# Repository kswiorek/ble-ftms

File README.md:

# Arduino BLE Indoor Bike Fitness Machine

This project uses two ESP32 boards to emulate an expensive indoor bike trainer and a power meter.<br/>
<br/>
One ESP measures power and cadence on a crank, the other receives these values, emulates a trainer and forwards the data. It also receives the simulation parameter from a computer and sets position of the resistance screw accordingly.<br/>
The data is also displayed on a 12864 screen and the user is able to change the resistance in ERG mode and the gears in simulation mode.<br/>
The user can also load a file with resistance values and times when to set them on an SD card.<br/>
The whole "realistic physics" part turned out to be more annoying to set up than realistic, so I added a configurator, with which the user can graphicaly define the function converting from the simulated grade to the resistance. More described in the instructable.
<br/><br/>
The promissed instructable <a href="https://www.instructables.com/DIY-Indoor-Bike-Smart-Trainer/?cb=1604870523">https://www.instructables.com/DIY-Indoor-Bike-Smart-Trainer/?cb=1604870523</a>

If you want to dig deaper into the code I highly suggest reading the "Fitness Machine Service" specifications
<a href="https://www.bluetooth.com/specifications/gatt/">https://www.bluetooth.com/specifications/gatt/</a>

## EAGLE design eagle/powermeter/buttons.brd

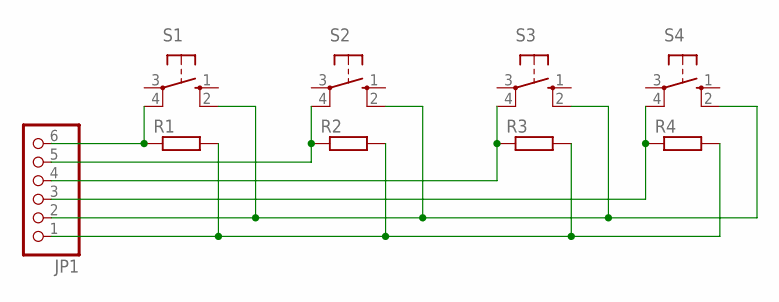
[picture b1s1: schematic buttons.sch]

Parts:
JP1: PINHD-1X6/90; 1X06/90
R1, R2, R3, R4: R-EU_0207/10; 0207/10
S1, S2, S3, S4: 10-XX; B3F-10XX

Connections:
unnamed: JP1.6, R1.1, S1.4 (P1)
unnamed: JP1.5, R2.1, S2.4 (P1)
unnamed: JP1.4, R3.1, S3.4 (P1)
unnamed: JP1.3, R4.1, S4.4 (P1)
unnamed: JP1.2, S1.2 (S1), S2.2 (S1), S3.2 (S1), S4.2 (S1)
unnamed: JP1.1, R1.2, R2.2, R3.2, R4.2

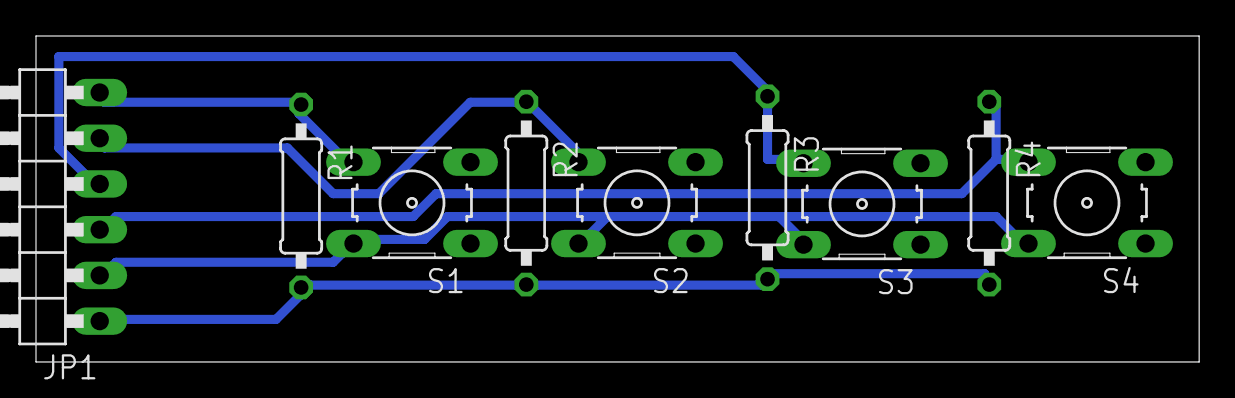
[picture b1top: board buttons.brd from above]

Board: 2 copper layers, 64.6 x 18.1 mm, 9 parts (0 on the bottom side), 6 nets.

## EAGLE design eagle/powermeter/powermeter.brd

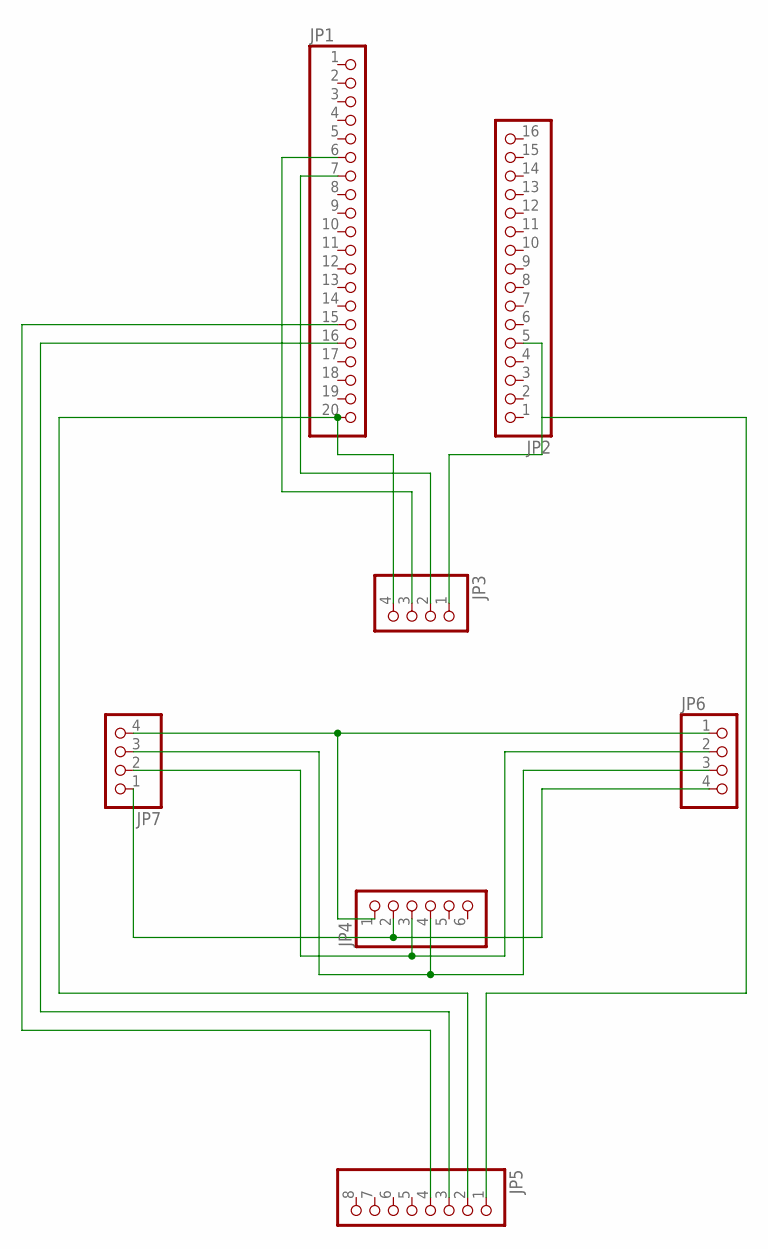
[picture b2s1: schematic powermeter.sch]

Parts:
JP1: PINHD-1X20; 1X20
JP2: PINHD-1X16; 1X16
JP3, JP6, JP7: PINHD-1X4; 1X04
JP4: PINHD-1X6; 1X06
JP5: PINHD-1X8; 1X08

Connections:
unnamed: JP4.1, JP6.1, JP7.4
unnamed: JP4.2, JP6.4, JP7.1
unnamed: JP4.3, JP6.2, JP7.2
unnamed: JP4.4, JP6.3, JP7.3
unnamed: JP1.20, JP3.4, JP5.2
unnamed: JP1.6, JP3.3
unnamed: JP1.7, JP3.2
unnamed: JP1.15, JP5.4
unnamed: JP2.5, JP3.1, JP5.1
unnamed: JP1.16, JP5.3

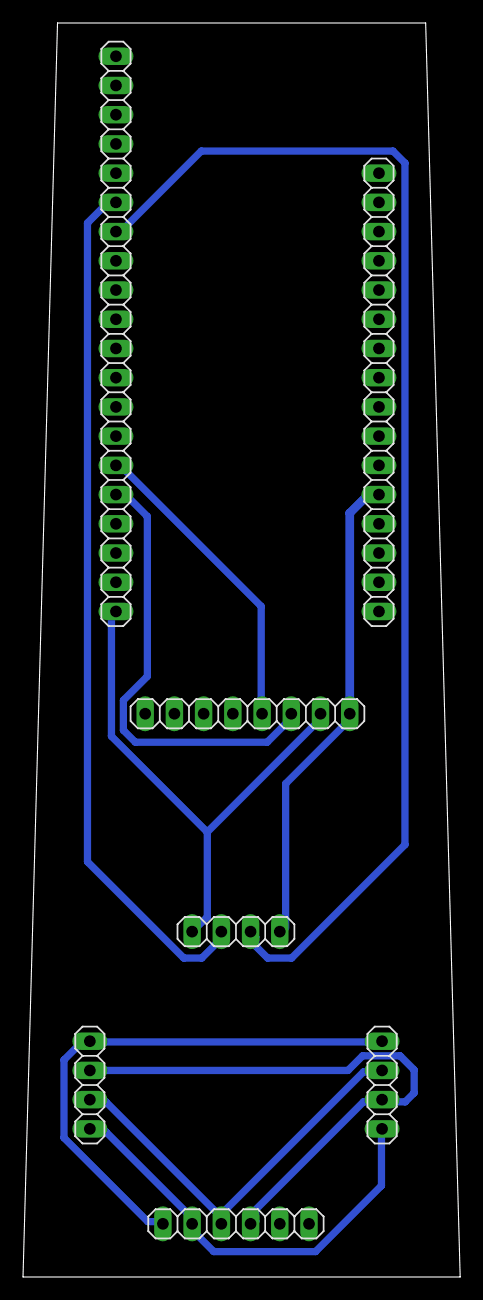
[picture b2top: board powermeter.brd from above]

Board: 2 copper layers, 38.0 x 109.0 mm, 7 parts (0 on the bottom side), 10 nets.

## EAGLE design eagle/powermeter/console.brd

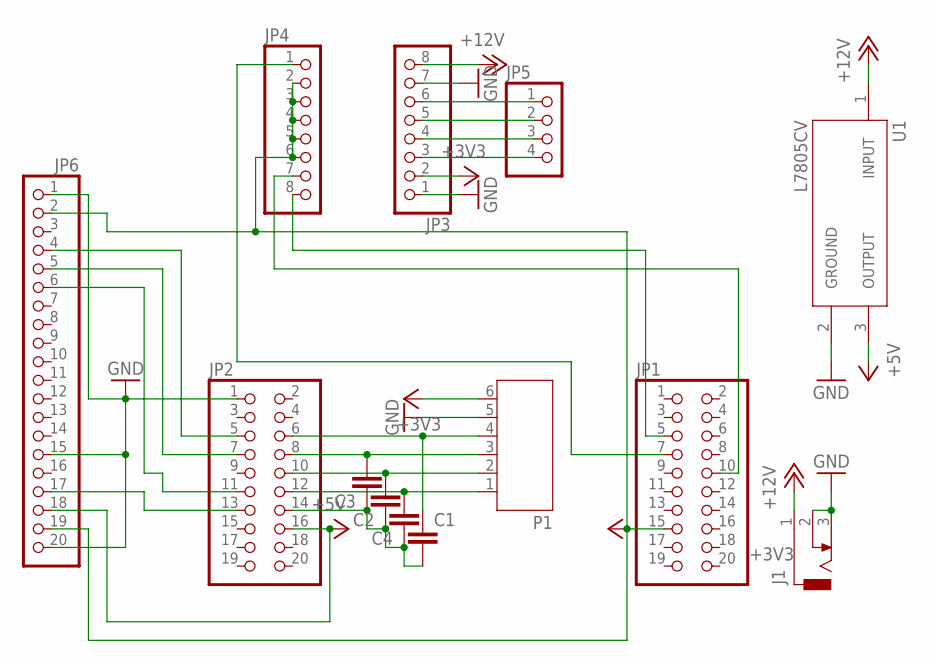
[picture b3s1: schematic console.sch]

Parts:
C1, C2, C3, C4: C-EU025-030X050; C025-030X050
J1: DCJ0303
JP1, JP2: PINHD-2X10; 2X10
JP3, JP4: PINHD-1X8; 1X08
JP5: PINHD-1X4/90; 1X04/90
JP6: PINHD-1X20; 1X20
P1: JST-PH6
U1: L7805CV; TO255P1040X460X1968-3

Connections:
+3V3: JP1.15, JP3.2, JP4.2, JP4.3, JP4.4, JP4.5, JP4.6, JP6.2, JP6.19, P1.6
+5V: JP2.16, JP6.18, U1.3 (OUTPUT)
+12V: J1.1, JP3.8, U1.1 (INPUT)
GND: J1.2, J1.3, JP2.1, JP3.1, JP3.7, JP6.1, JP6.15, JP6.20, P1.5, U1.2 (GROUND)
unnamed: C2.2, JP2.10, P1.2
unnamed: C3.2, JP2.8, P1.3
unnamed: C1.1, JP2.6, P1.4
unnamed: JP2.5, JP6.4
unnamed: JP2.13, JP6.17
unnamed: JP2.7, JP6.5
unnamed: C4.2, JP2.12, P1.1
unnamed: JP1.7, JP4.1
unnamed: JP3.6, JP5.1
unnamed: JP1.10, JP4.7
unnamed: JP1.5, JP4.8
unnamed: JP3.5, JP5.2
unnamed: JP3.4, JP5.3
unnamed: JP3.3, JP5.4
unnamed: C1.2, C2.1, C3.1, C4.1, JP2.14
unnamed: JP2.11, JP6.6

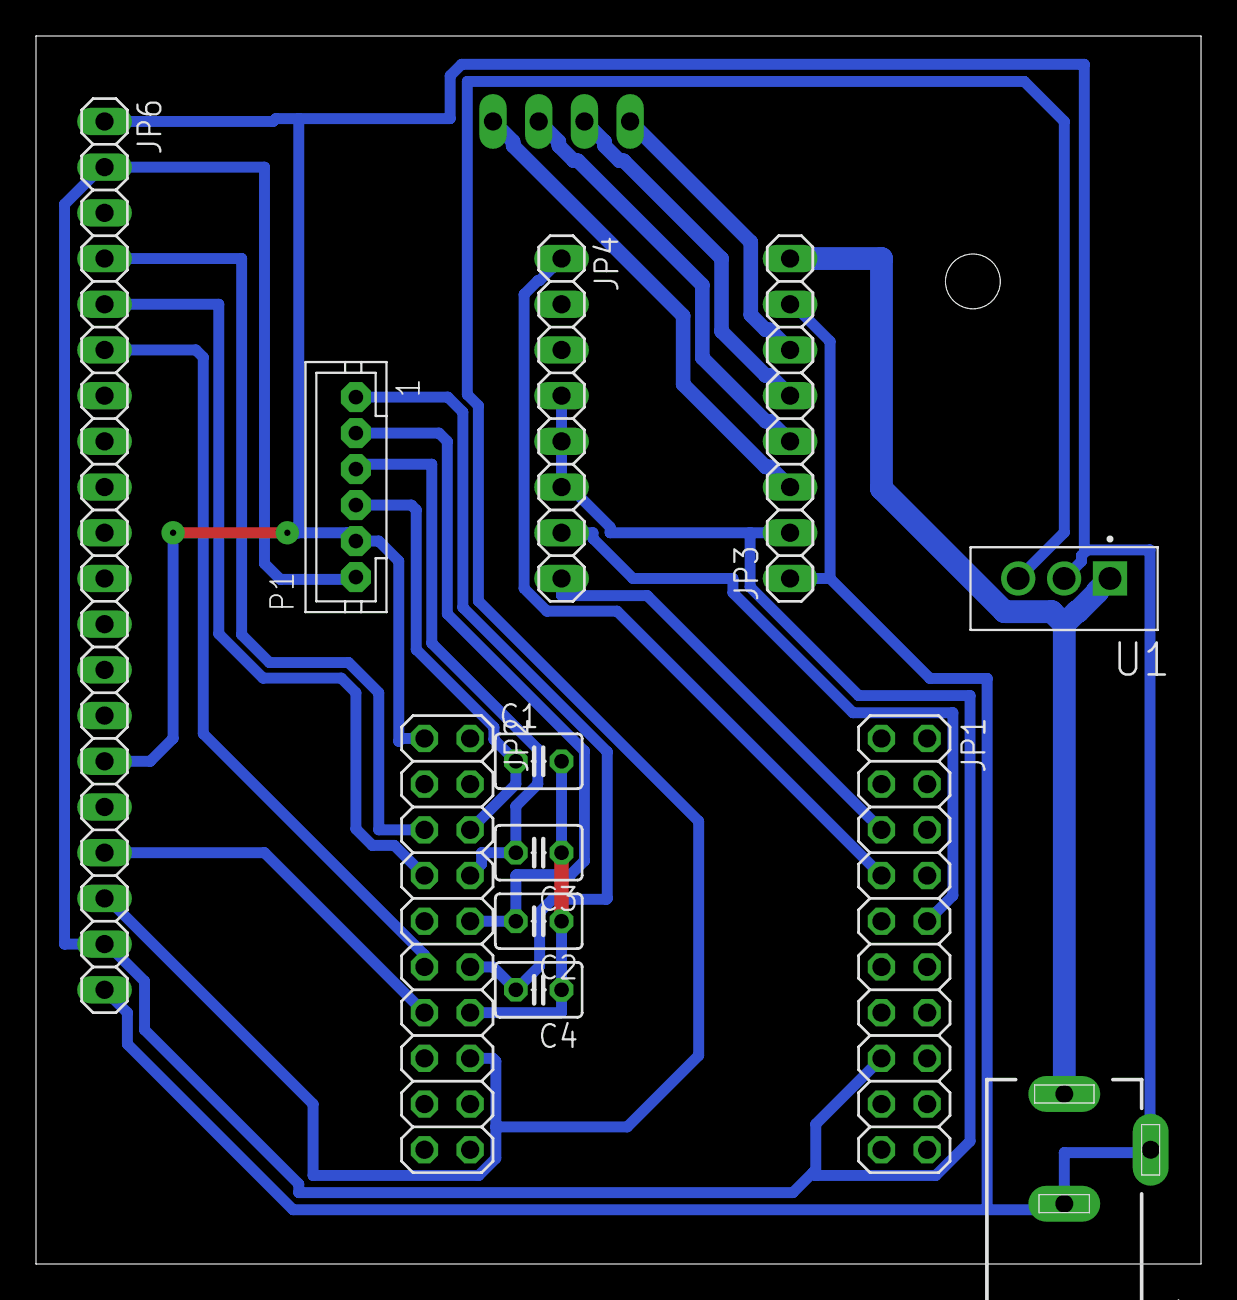
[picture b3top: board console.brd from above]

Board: 2 copper layers, 64.8 x 68.2 mm, 13 parts (1 on the bottom side), 20 nets.

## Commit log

2020-05-18 Rename BLE.h to indoorBike/BLE.h
2020-05-18 Rename indoorBike_final2.ino to indoorBike/indoorBike.ino
2020-05-18 Rename cp_withpower_avg.ino to indoorBike/powerCrank/powerCrank.ino
2020-05-18 Rename indoorBike/indoorBike.ino to indoorBike/console/console.ino
2020-05-18 Rename indoorBike/BLE.h to indoorBike/console/BLE.h
2020-11-08 Create folder
2020-11-08 Add files via upload
    Added the Autodesk EAGLE project
2020-11-08 Add files via upload
    Remaining project files
2020-11-08 Add files via upload
    Updated files and changed directories
2021-01-16 Added a configurator
2021-01-16 Rename config.py to configurator/config.py
2021-01-16 Modified for the configurator
2021-01-16 Rename configurator/config.py to configurator/code/config.py
2021-01-16 Rename configurator/code/config.py to code/configurator/config.py
2022-07-20 Added advertising flags
    3 days of debugging why RGT doesn't connect, one line added :)
    When the device sees those two flags it works for some reason, while iPhones do not care.
